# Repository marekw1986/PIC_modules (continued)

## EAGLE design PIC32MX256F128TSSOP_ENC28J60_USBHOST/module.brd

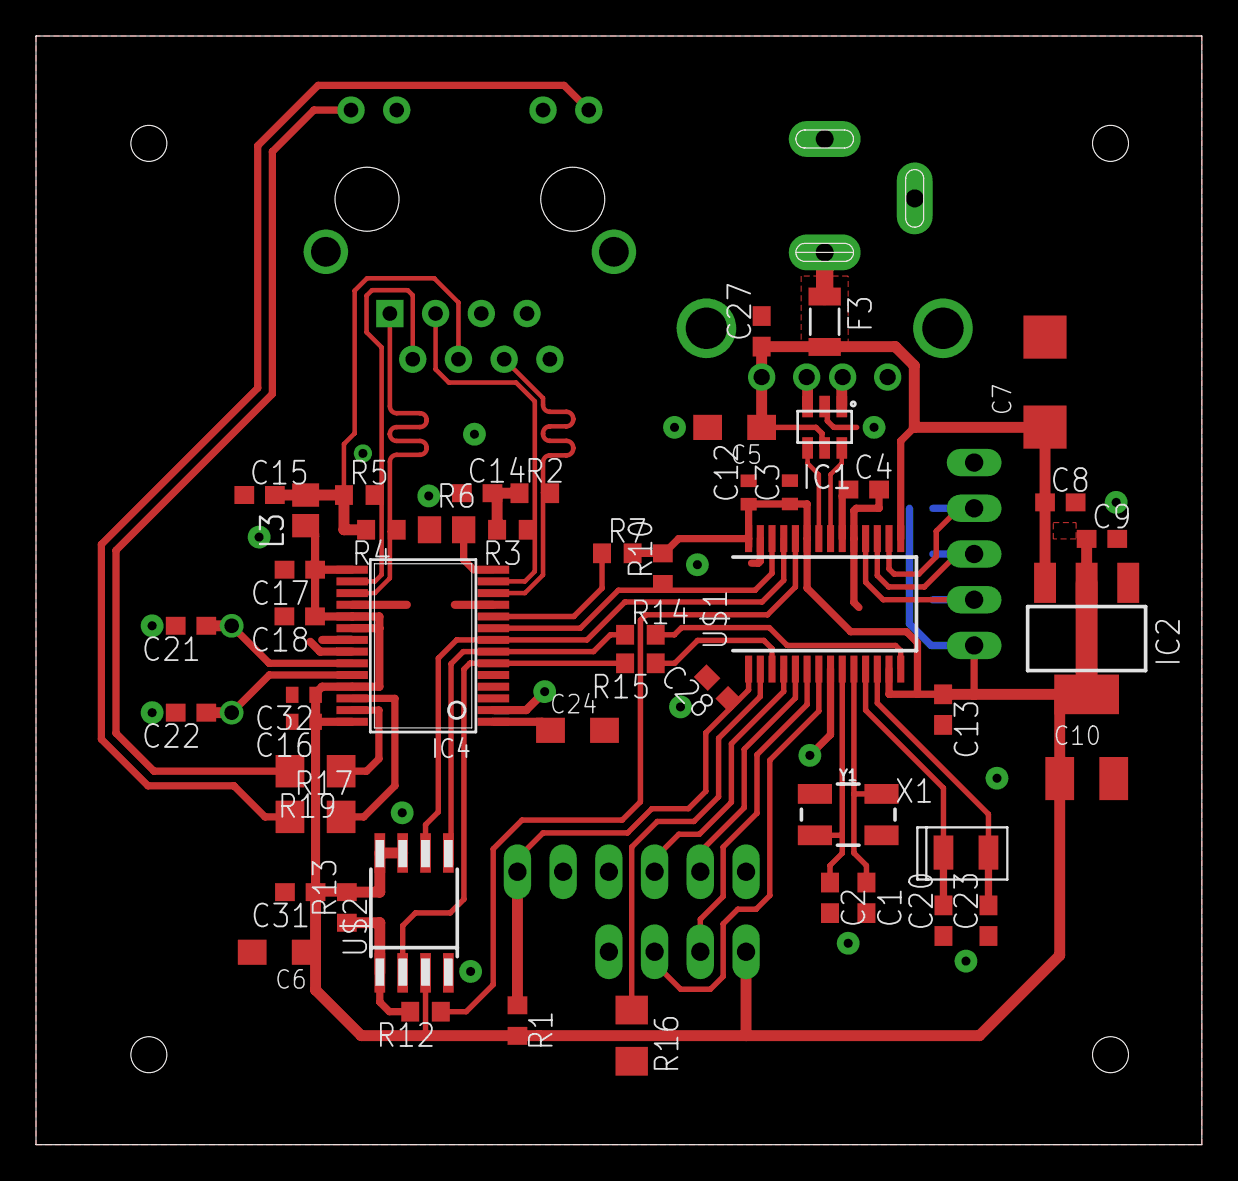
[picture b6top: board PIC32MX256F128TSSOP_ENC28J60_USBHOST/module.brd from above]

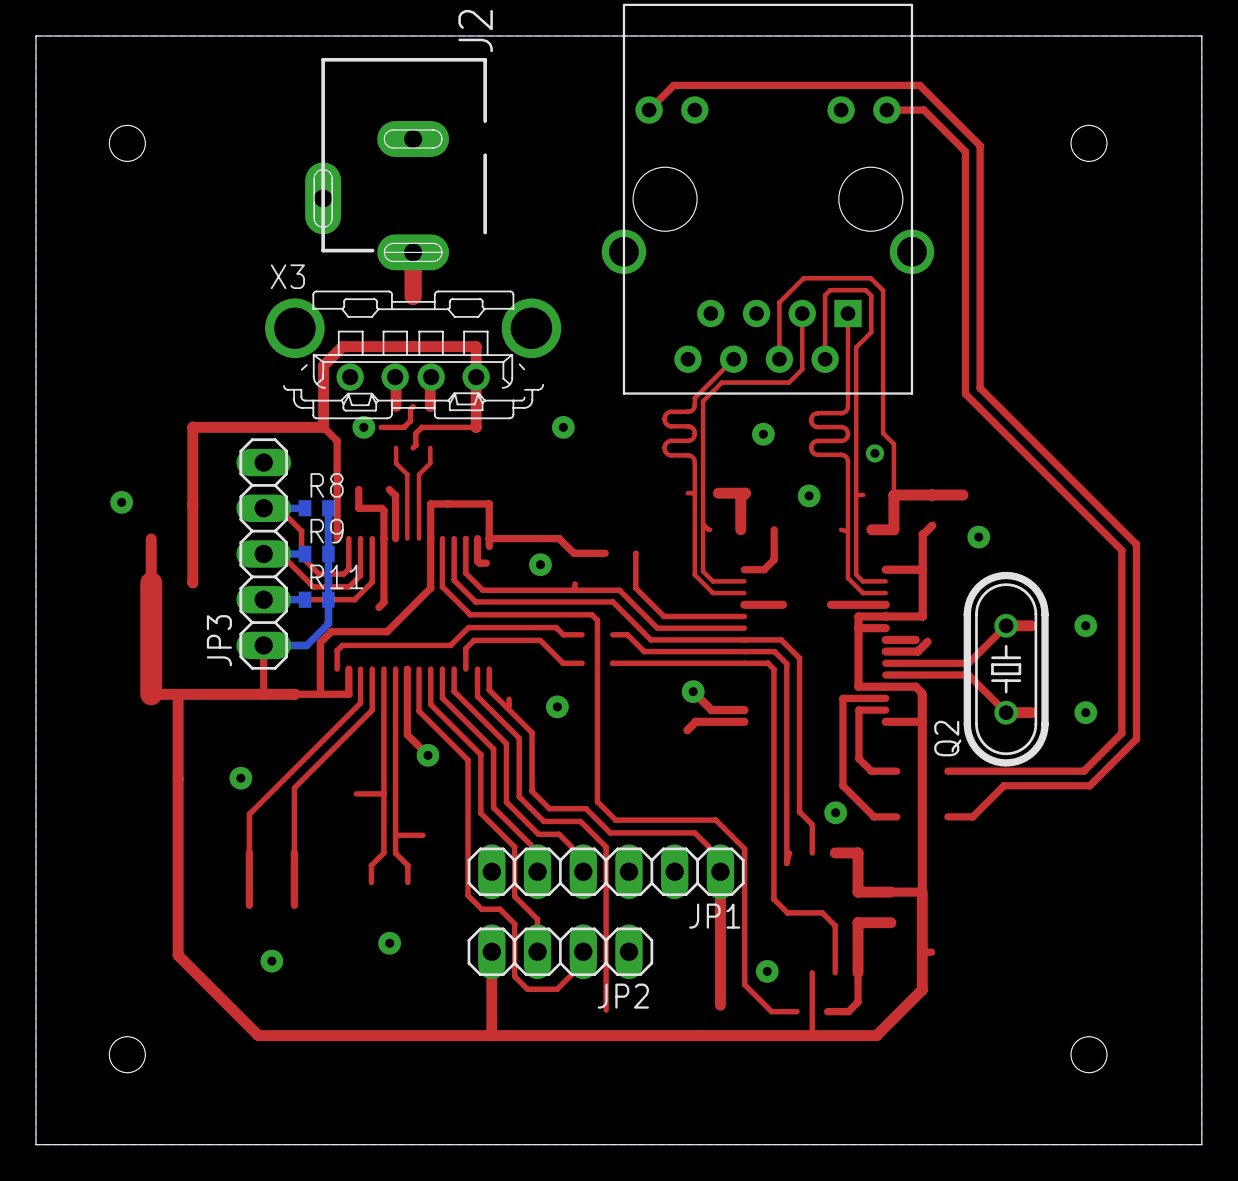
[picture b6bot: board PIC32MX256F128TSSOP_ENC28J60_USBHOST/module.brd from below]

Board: 2 copper layers, 64.8 x 61.6 mm, 60 parts (10 on the bottom side), 45 nets.

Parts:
C1, C2, C4, C8, C9, C13, C14, C15, C17, C18, C20, C21, C22, C23, C27, C28: C0603
C3, C12, C16, C32: C0402
C5, C6, C24: SMC_A
C7: SMC_C
C10: SMC_B
C31: 100nF; C0603
F3: 1206L012; 1206L
IC1: IC_USBLC6-2; SOT-23-6L
IC2: LM1117IMPX-3.3; SOT223
IC4: ENC28J60; TSSOP28W
J2: POWER_JACKSLT; POWER_JACK_SLOT
JP1: 1X06
JP2: 1X04
JP3: 1X05
L3: FB805
Q2: HC49/S
R1, R2, R3, R4, R5, R7, R10, R14, R15: R0603
R6: R0805
R8, R9, R11: R0402
R12: 0R; R0603
R13: 10k?; R0603
R16, R17, R19: R1206
RJ1: HR911105A
U$1: PIC32MX250F128B2; SSOP28
U$2: SST25VF016BSO8M; SO-08M
X1: CRYSTALS-NOGND-CFPX-217; 3.2X1.5-2-PAD
X3: KUSBVX
Y1: CRYSTAL-GROUNDEDSMD-5X3.2; CRYSTAL-SMD-5X3.2-4PAD

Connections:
CE: R12.1, U$1.24
CE1: R12.2, R13.1, U$2.1
D_N: IC1.4, U$1.22
D_P: IC1.6, U$1.21
ENC_CS: IC4.P$9, R10.1, U$1.26
ENC_RST: IC4.P$10, R7.1
GND: C1.2, C2.2, C3.2, C4.2, C5.-, C6.-, C7.-, C8.2, C9.2, C10.-, C12.2, C13.2, C14.1, C15.1, C16.2, C17.2, C18.2, C20.1, C21.2, C22.2, C23.1, C24.-, C27.2, C28.2, C31.2, C32.2, IC1.2, IC2.1, IC4.P$2, IC4.P$11, IC4.P$18, IC4.P$21, IC4.P$22, J2.GND@1, J2.GND@2, JP1.3, JP2.1, JP3.5, R6.1, RJ1.G-, RJ1.GND, RJ1.SHIELD0, RJ1.SHIELD1, RJ1.Y-, U$1.8, U$1.19, U$1.27, U$2.4, X3.4, X3.M1, X3.M2, Y1.2, Y1.4
IO_INT: JP3.4, R8.1, U$1.16
LEDA: IC4.P$27, R19.1
LEDB: IC4.P$26, R17.2
MCLR: C28.1, JP1.1, R1.1, U$1.1
MISO: IC4.P$6, R15.2, U$2.2
MOSI: IC4.P$7, R14.1, U$2.5
unnamed: C14.2, R2.1, R3.2
unnamed: C15.2, L3.2, R4.2, R5.1, RJ1.P4
unnamed: C4.1, U$1.20
unnamed: IC1.1, X3.3
unnamed: IC1.3, X3.2
unnamed: IC4.P$14, R6.2
unnamed: R14.2, U$1.14
unnamed: F3.1, J2.PWR
unnamed: R15.1, U$1.3
unnamed: R16.1, U$1.2
unnamed: C1.1, U$1.10, Y1.3
unnamed: C2.1, U$1.9, Y1.1
unnamed: C21.1, IC4.P$23, Q2.2
unnamed: C22.1, IC4.P$24, Q2.1
unnamed: C24.+, IC4.P$1
unnamed: R17.1, RJ1.Y+
unnamed: R19.2, RJ1.G+
PGEC: JP1.5, U$1.5
PGED: JP1.4, U$1.4
RXD: JP2.3, U$1.6
SCK: IC4.P$8, U$1.25, U$2.6
SCL: JP3.3, R9.1, U$1.17
SDA: JP3.2, R11.1, U$1.18
SOSCI: C20.2, U$1.11, X1.1
SOSCO: C23.2, U$1.12, X1.2
TPIN_N: IC4.P$12, R2.2, RJ1.RD-
TPIN_P: IC4.P$13, R3.1, RJ1.RD+
TPOUT_N: IC4.P$16, R5.2, RJ1.TD-
TPOUT_P: IC4.P$17, R4.1, RJ1.TD+
TXD: JP2.2, U$1.7
VBUS: C5.+, C7.+, C8.1, C27.1, F3.2, IC1.5, IC2.3, U$1.15, X3.1
_3V: C3.1, C6.+, C9.1, C10.+, C12.1, C13.1, C16.1, C17.1, C18.1, C31.1, C32.1, IC2.2, IC2.TAB, IC4.P$15, IC4.P$19, IC4.P$20, IC4.P$25, IC4.P$28, JP2.4, JP3.1, L3.1, R1.2, R7.2, R8.2, R9.2, R10.2, R11.2, R13.2, U$1.13, U$1.23, U$1.28, U$2.3, U$2.7, U$2.8

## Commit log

2020-09-22 some changes
2020-12-14 PCB updated
2020-12-14 PCB updates
2020-12-15 DP83848 RST line added
2020-12-18 Test
2020-12-20 Crystl generator added
2020-12-20 Minor changes
2020-12-21 Some updates
2020-12-28 Ethernet AVDD filtering
2022-10-11 MISO pull-ups added
2023-02-06 Additional board added
2023-02-06 Additional boards added
